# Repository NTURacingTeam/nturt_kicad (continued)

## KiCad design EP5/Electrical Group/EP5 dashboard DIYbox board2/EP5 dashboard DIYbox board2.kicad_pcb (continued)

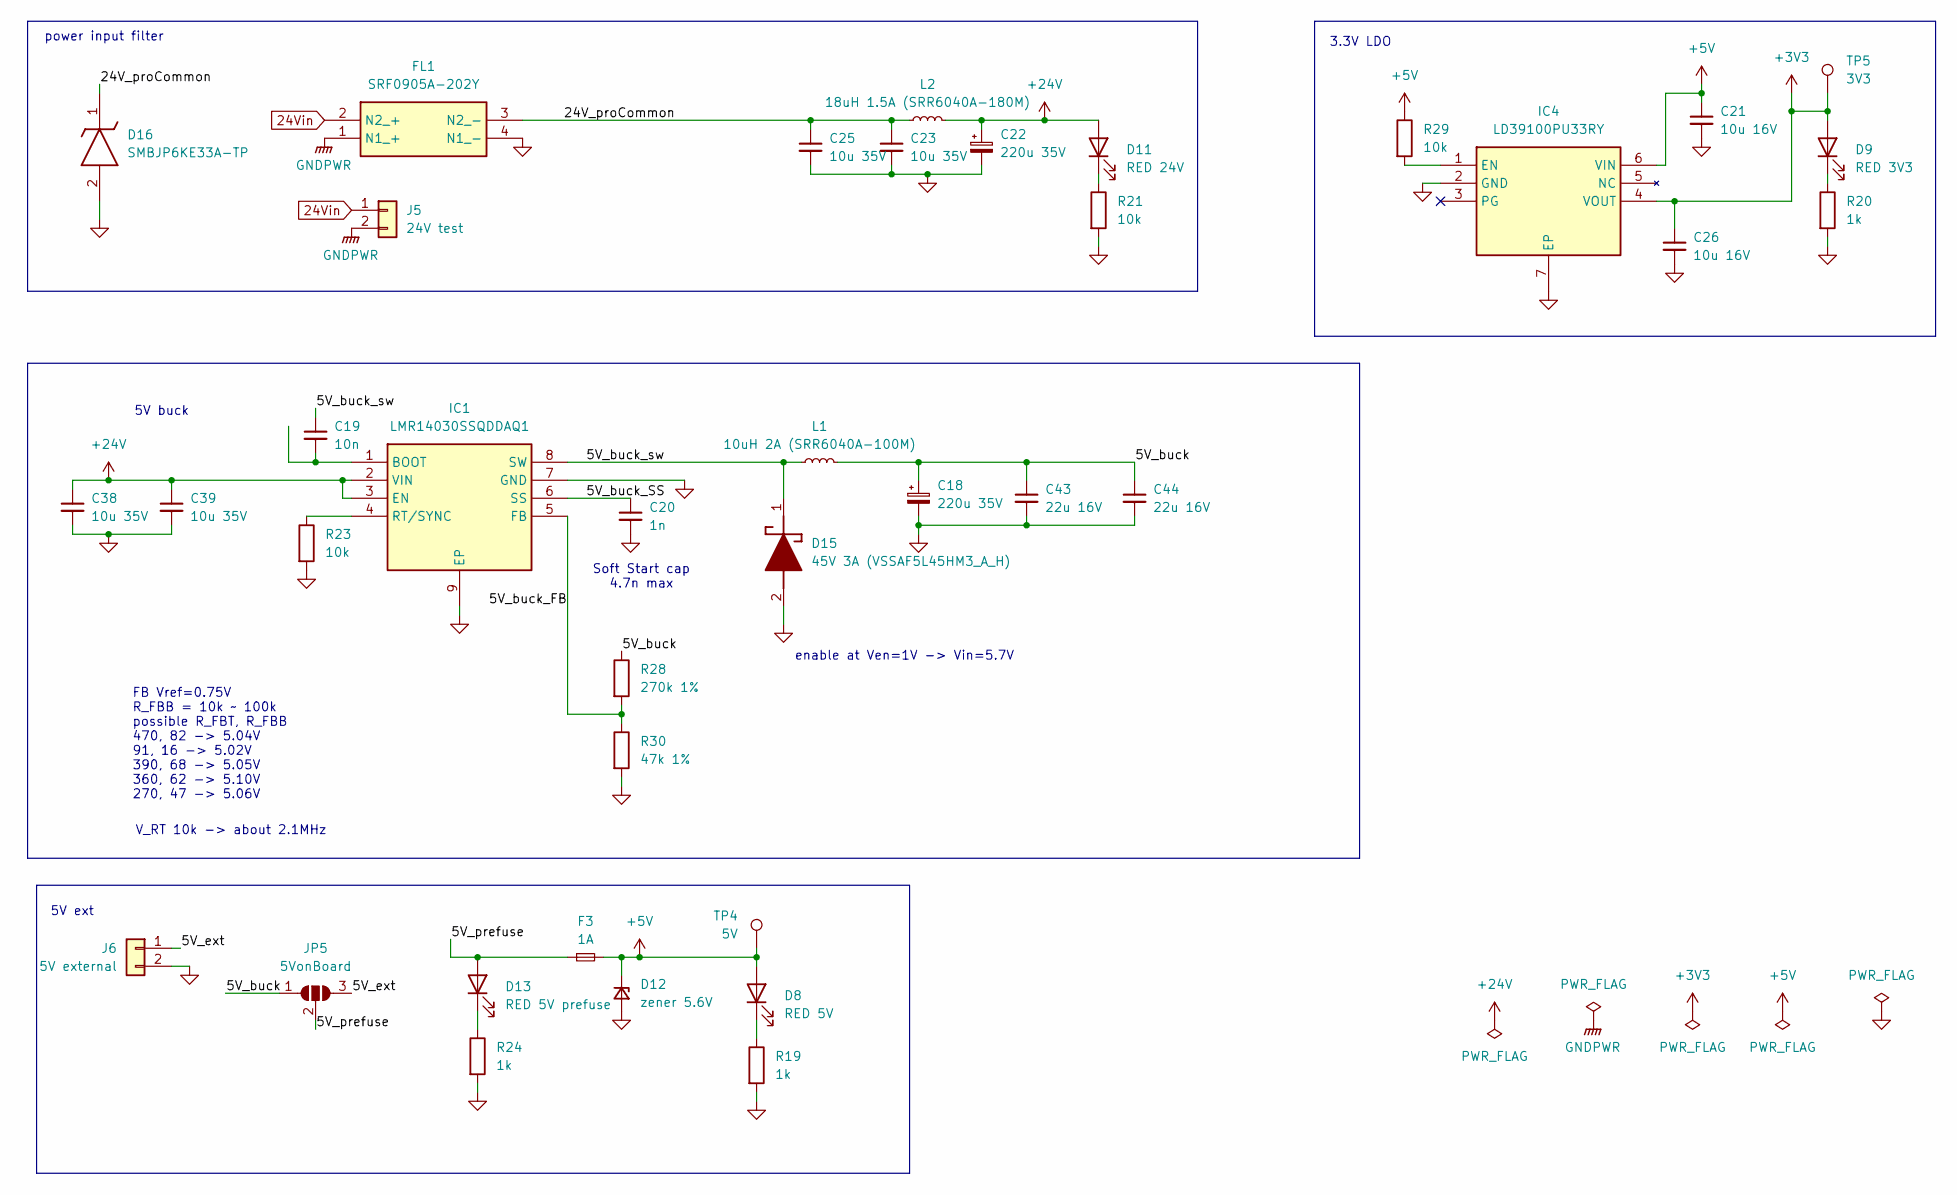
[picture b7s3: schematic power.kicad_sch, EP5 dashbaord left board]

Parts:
C18, C22: 220u 35V; CP_Radial_D8.0mm_P3.80mm
C19: 10n; C_0603_1608Metric
C20: 1n; C_0603_1608Metric
C21, C26: 10u 16V; C_0805_2012Metric
C23, C25, C38, C39: 10u 35V; C_1206_3216Metric
C43, C44: 22u 16V; C_1206_3216Metric
D8: RED 5V; LED_0603_1608Metric
D9: RED 3V3; LED_0603_1608Metric
D11: RED 24V; LED_0603_1608Metric
D12: zener 5.6V; D_MiniMELF
D13: RED 5V prefuse; LED_0603_1608Metric
D15: 45V 3A (VSSAF5L45HM3_A_H); SODFL5226X100N; Mouser Part Number 78-VSSAF5L45HM3_A/H
D16: SMBJP6KE33A-TP; DIOM5336X262N; Mouser Part Number 833-SMBJP6KE33A-TP
F3: 1A; Fuse_2512_6332Metric_Pad1.52x3.35mm_HandSolder
FL1: SRF0905A-202Y; SRF0905A102Y; Mouser Part Number 652-SRF0905A-202Y
IC1: LMR14030SSQDDAQ1; SOIC127P600X170-9N; Mouser Part Number 595-LMR14030SSQDDAQ1
IC4: LD39100PU33RY; SON95P300X300X90-7N-D; Mouser Part Number 511-LD39100PU33RY
J5: 24V test; JST_XH_B2B-XH-A_1x02_P2.50mm_Vertical
J6: 5V external; JST_XH_B2B-XH-A_1x02_P2.50mm_Vertical
JP5: 5VonBoard; SolderJumper-3_P1.3mm_Open_Pad1.0x1.5mm
L1: 10uH 2A (SRR6040A-100M); SRR6040A180M
L2: 18uH 1.5A (SRR6040A-180M); SRR6040A180M
R19, R20, R24: 1k; R_0603_1608Metric
R21, R23, R29: 10k; R_0603_1608Metric
R28: 270k 1%; R_0603_1608Metric
R30: 47k 1%; R_0603_1608Metric
TP4: 5V; TestPoint_Pad_D1.0mm
TP5: 3V3; TestPoint_Pad_D1.0mm

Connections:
24Vin: FL1.2 (N2_+), J5.1; also elsewhere on the board
+3V3: C26.1, D9.2 (A), IC4.4 (VOUT), TP5.1; also elsewhere on the board
+5V: C21.1, D8.2 (A), D12.1 (K), F3.2, IC4.6 (VIN), R29.1, TP4.1; also elsewhere on the board
+24V: C22.1, C38.1, C39.1, D11.2 (A), IC1.2 (VIN), IC1.3 (EN), L2.2
/power/5V_buck: C18.1, C43.1, C44.1, JP5.1 (A), L1.2, R28.1
/power/5V_buck_FB: IC1.5 (FB), R28.2, R30.1
/power/5V_buck_SS: C20.1, IC1.6 (SS)
/power/5V_buck_sw: C19.1, D15.1 (K), IC1.8 (SW), L1.1
/power/5V_ext: J6.1, JP5.3 (B)
/power/5V_prefuse: D13.2 (A), F3.1, JP5.2 (C)
/power/24V_proCommon: C23.1, C25.1, D16.1 (K), FL1.3 (N2_-), L2.1
GND: C18.2, C20.2, C21.2, C22.2, C23.2, C25.2, C26.2, C38.2, C39.2, C43.2, C44.2, D12.2 (A), D15.2 (A), D16.2 (A), FL1.4 (N1_-), IC1.7 (GND), IC1.9 (EP), IC4.2 (GND), IC4.7 (EP), J6.2, R19.2, R20.2, R21.2, R23.2, R24.2, R30.2; also elsewhere on the board
GNDPWR: FL1.1 (N1_+), J5.2; also elsewhere on the board
unnamed: D8.1 (K), R19.1
unnamed: D9.1 (K), R20.1
unnamed: D11.1 (K), R21.1
unnamed: D13.1 (K), R24.1
unnamed: C19.2, IC1.1 (BOOT)
unnamed: IC1.4 (RT/SYNC), R23.1
unnamed: IC4.1 (EN), R29.2

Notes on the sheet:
FB Vref=0.75V R_FBB = 10k ~ 100k possible R_FBT, R_FBB 470, 82 -> 5.04V 91, 16 -> 5.02V 390, 68 -> 5.05V 360, 62 -> 5.10V 270, 47 -> 5.06V
Soft Start cap 4.7n max
3.3V LDO
enable at Ven=1V -> Vin=5.7V
5V ext
5V buck
V_RT 10k -> about 2.1MHz
power input filter

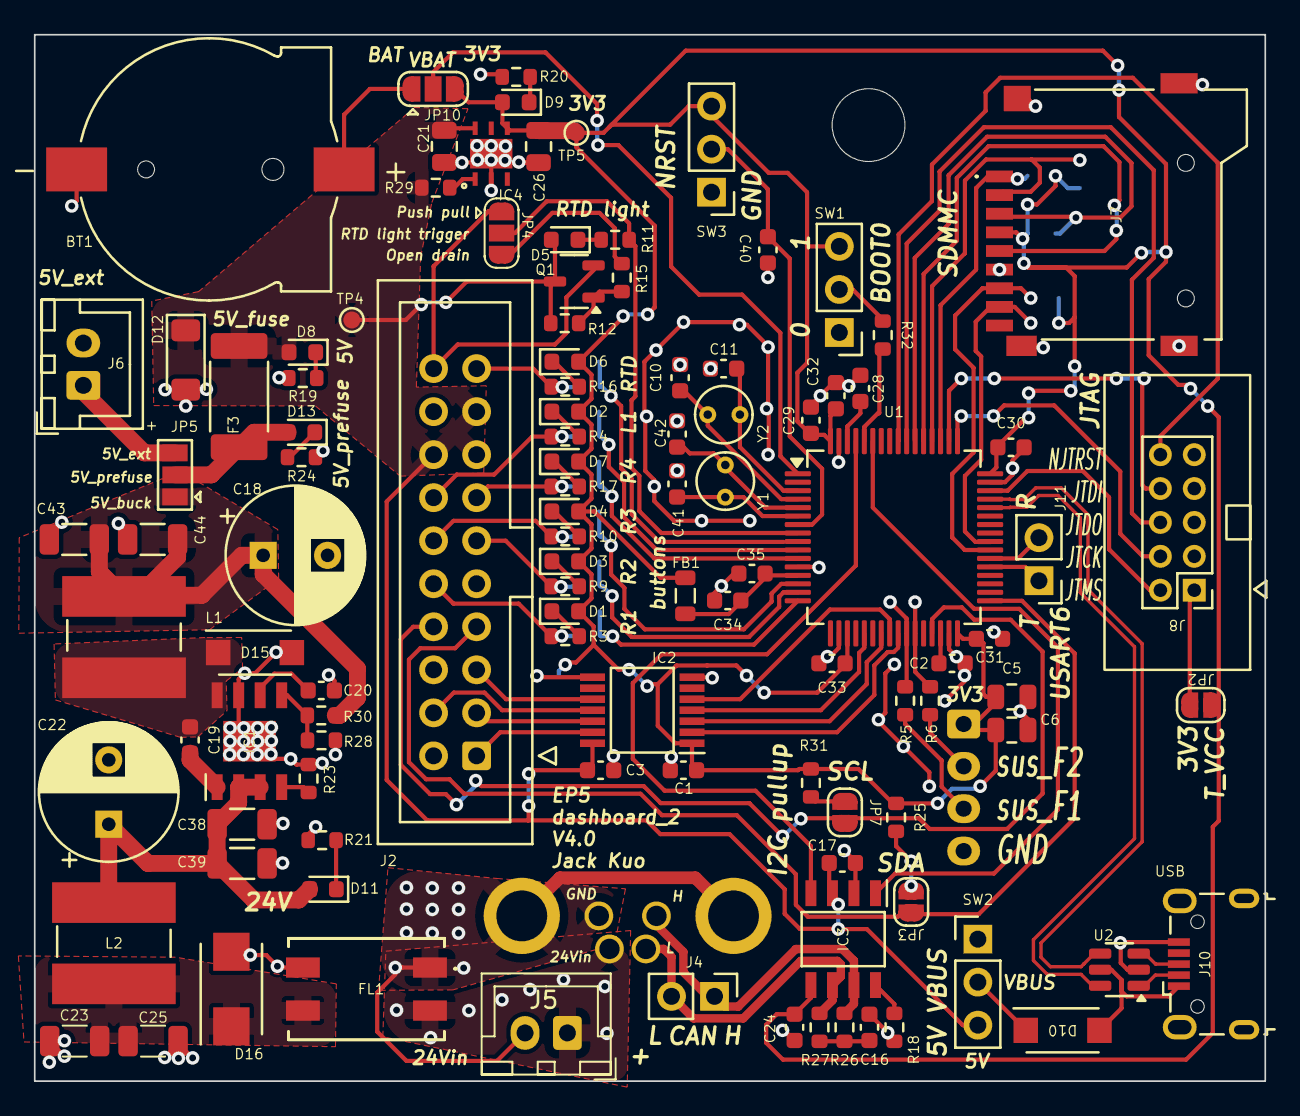
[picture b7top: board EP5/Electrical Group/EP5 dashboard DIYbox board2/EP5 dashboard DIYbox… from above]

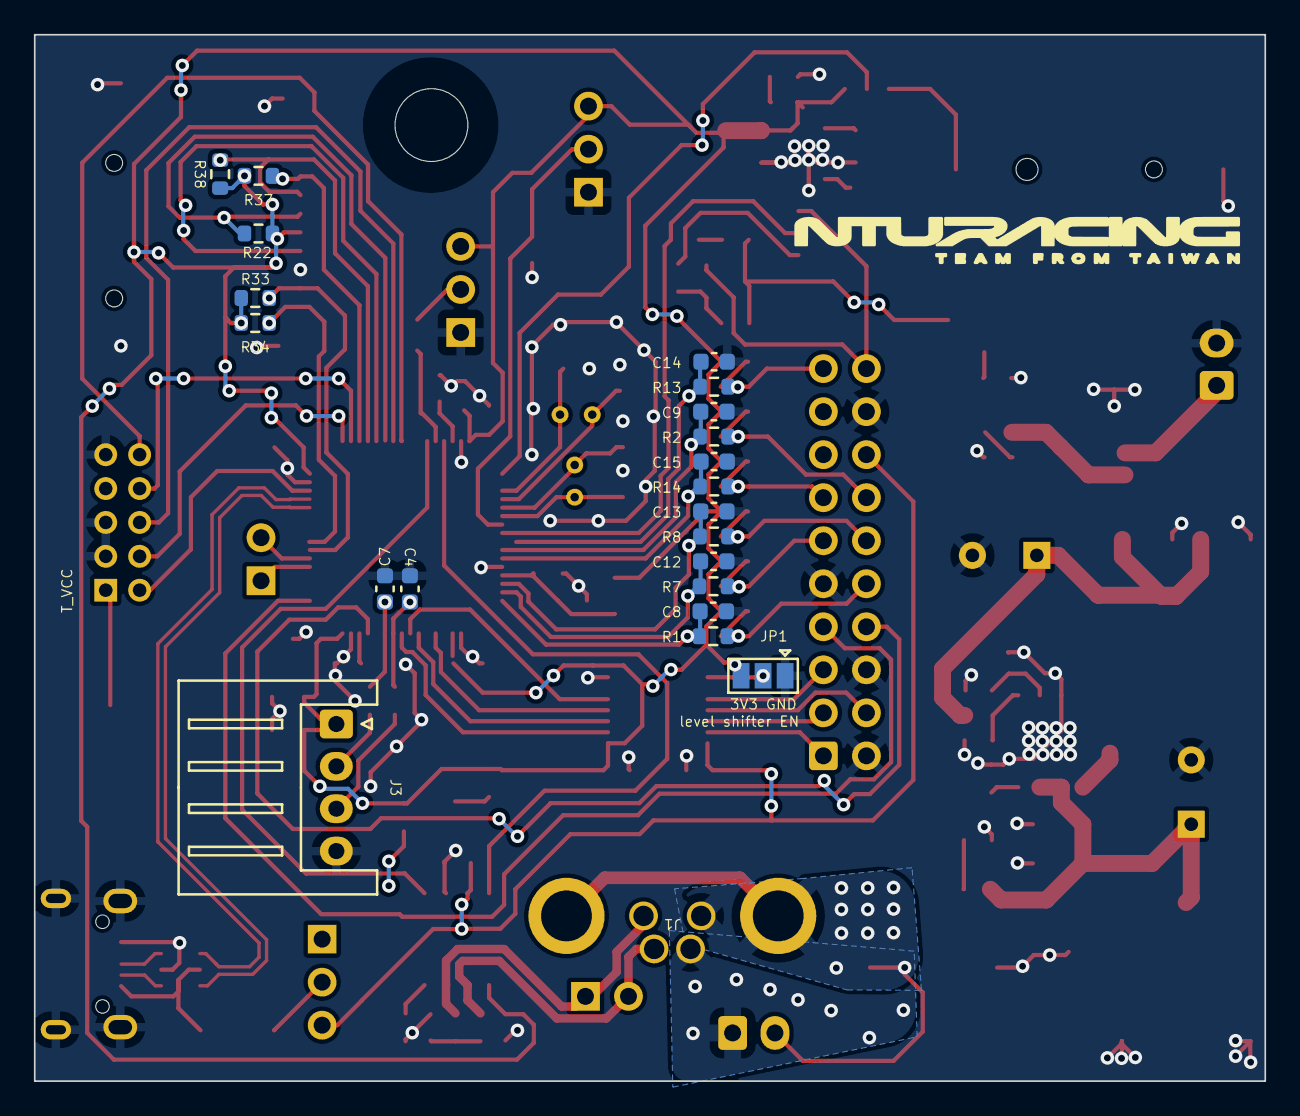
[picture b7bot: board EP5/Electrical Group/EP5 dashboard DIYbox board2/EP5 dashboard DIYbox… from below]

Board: 2 copper layers, 72.6 x 61.8 mm, 130 parts (22 on the bottom side), 98 nets.
